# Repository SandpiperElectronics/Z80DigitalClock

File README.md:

# Z80 Digital Clock

## Description:
Built out of a Z80 microcomputer system of my own design, this clock can display Hours, Minutes, and Seconds and does so using an interupt from an Intel 82C53 Counter/Timer chip that is equally as vintage as the Z80.

## To Do: 
- [X] Clock Display
- [X] Clock Display PCB
- [X] Reset Circuit
- [X] Basic Functionality (ROM and CPU)
- [X] 8255 Peripheral Chip
- [X] 8253 Counter/Timer
- [ ] Write Display Sub Routine
- [ ] Clock Sub Routine
- [X] Buttons to Set time
- [ ] Sub routine for button input
- [ ] Z80 Clock PCB

## Images:

### Z80 Clock Schematic (New Version)

### Z80 Clock Schematic (Old Version)

### 7 Segment Peripheral Schematic

### 7 Segment Peripheral Board Design

### 7 Segment PCB and Z80 Clock
.JPG)

### 7 Segments in the Dark
.JPG)

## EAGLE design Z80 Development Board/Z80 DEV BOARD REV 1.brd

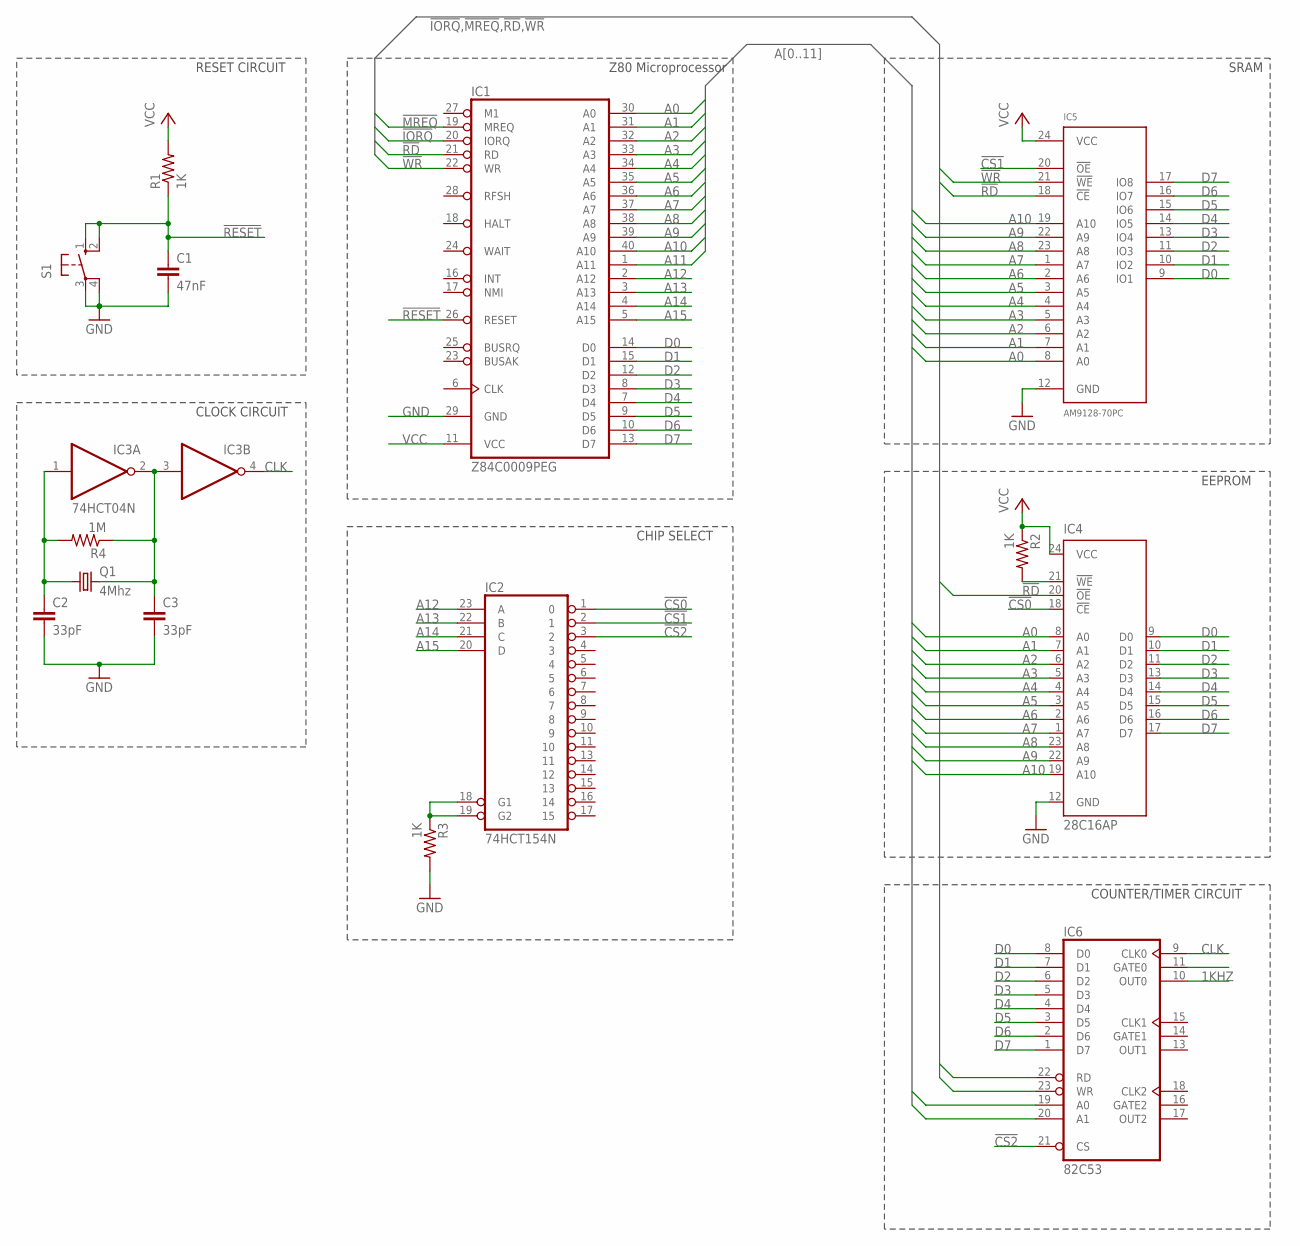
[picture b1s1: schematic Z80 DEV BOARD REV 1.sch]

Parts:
C1: 47nF; C050-035X075
C2, C3: 33pF; C050-035X075
IC1: Z84C0009PEG; DIL40
IC2: 74HCT154N; DIL24-6
IC3: 74HCT04N; DIL14
IC4: 28C16AP; DIL24-6
IC5: AM9128-70PC; DIL24-6
IC6: 82C53; DIL24-6
Q1: 4Mhz; HC49/S
R1, R2, R3: 1K; 0207/7
R4: 1M; 0207/7
S1: 10-XX; B3F-10XX

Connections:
1KHZ: IC6.10 (OUT0)
!CS0: IC2.1 (0), IC4.18 (!CE)
!CS1: IC2.2 (1), IC5.20 (!OE)
!CS2: IC2.3 (2), IC6.21 (CS)
!IORQ: IC1.20 (IORQ)
!MREQ: IC1.19 (MREQ)
!RD: IC1.21 (RD), IC4.20 (!OE), IC5.18 (!CE), IC6.22 (RD)
!RESET: C1.1, IC1.26 (RESET), R1.1, S1.1 (S), S1.2 (S1)
!WR: IC1.22 (WR), IC5.21 (!WE), IC6.23 (WR)
A0: IC1.30 (A0), IC4.8 (A0), IC5.8 (A0), IC6.19 (A0)
A1: IC1.31 (A1), IC4.7 (A1), IC5.7 (A1), IC6.20 (A1)
A2: IC1.32 (A2), IC4.6 (A2), IC5.6 (A2)
A3: IC1.33 (A3), IC4.5 (A3), IC5.5 (A3)
A4: IC1.34 (A4), IC4.4 (A4), IC5.4 (A4)
A5: IC1.35 (A5), IC4.3 (A5), IC5.3 (A5)
A6: IC1.36 (A6), IC4.2 (A6), IC5.2 (A6)
A7: IC1.37 (A7), IC4.1 (A7), IC5.1 (A7)
A8: IC1.38 (A8), IC4.23 (A8), IC5.23 (A8)
A9: IC1.39 (A9), IC4.22 (A9), IC5.22 (A9)
A10: IC1.40 (A10), IC4.19 (A10), IC5.19 (A10)
A11: IC1.1 (A11)
A12: IC1.2 (A12), IC2.23 (A)
A13: IC1.3 (A13), IC2.22 (B)
A14: IC1.4 (A14), IC2.21 (C)
A15: IC1.5 (A15), IC2.20 (D)
CLK: IC3.4 (O), IC6.9 (CLK0)
D0: IC1.14 (D0), IC4.9 (D0), IC5.9 (IO1), IC6.8 (D0)
D1: IC1.15 (D1), IC4.10 (D1), IC5.10 (IO2), IC6.7 (D1)
D2: IC1.12 (D2), IC4.11 (D2), IC5.11 (IO3), IC6.6 (D2)
D3: IC1.8 (D3), IC4.13 (D3), IC5.13 (IO4), IC6.5 (D3)
D4: IC1.7 (D4), IC4.14 (D4), IC5.14 (IO5), IC6.4 (D4)
D5: IC1.9 (D5), IC4.15 (D5), IC5.15 (IO6), IC6.3 (D5)
D6: IC1.10 (D6), IC4.16 (D6), IC5.16 (IO7), IC6.2 (D6)
D7: IC1.13 (D7), IC4.17 (D7), IC5.17 (IO8), IC6.1 (D7)
GND: C1.2, C2.2, C3.2, IC1.29 (GND), IC2.12 (GND), IC3.7 (GND), IC4.12 (GND), IC5.12 (GND), IC6.12 (GND), R3.2, S1.3, S1.4 (P1)
unnamed: C2.1, IC3.1 (I), Q1.1, R4.2
unnamed: IC4.21 (!WE), R2.2
unnamed: C3.1, IC3.2 (O), IC3.3 (I), Q1.2, R4.1
unnamed: IC2.18 (G1), IC2.19 (G2), R3.1
VCC: IC1.11 (VCC), IC2.24 (VCC), IC3.14 (VCC), IC4.24 (VCC), IC5.24 (VCC), IC6.24 (VCC), R1.2, R2.1

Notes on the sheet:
RESET CIRCUIT
Z80 Microprocessor
EEPROM
SRAM
CHIP SELECT
CLOCK CIRCUIT
COUNTER/TIMER CIRCUIT

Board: 2 copper layers, 15 parts (0 on the bottom side), 36 nets, no tracks yet.

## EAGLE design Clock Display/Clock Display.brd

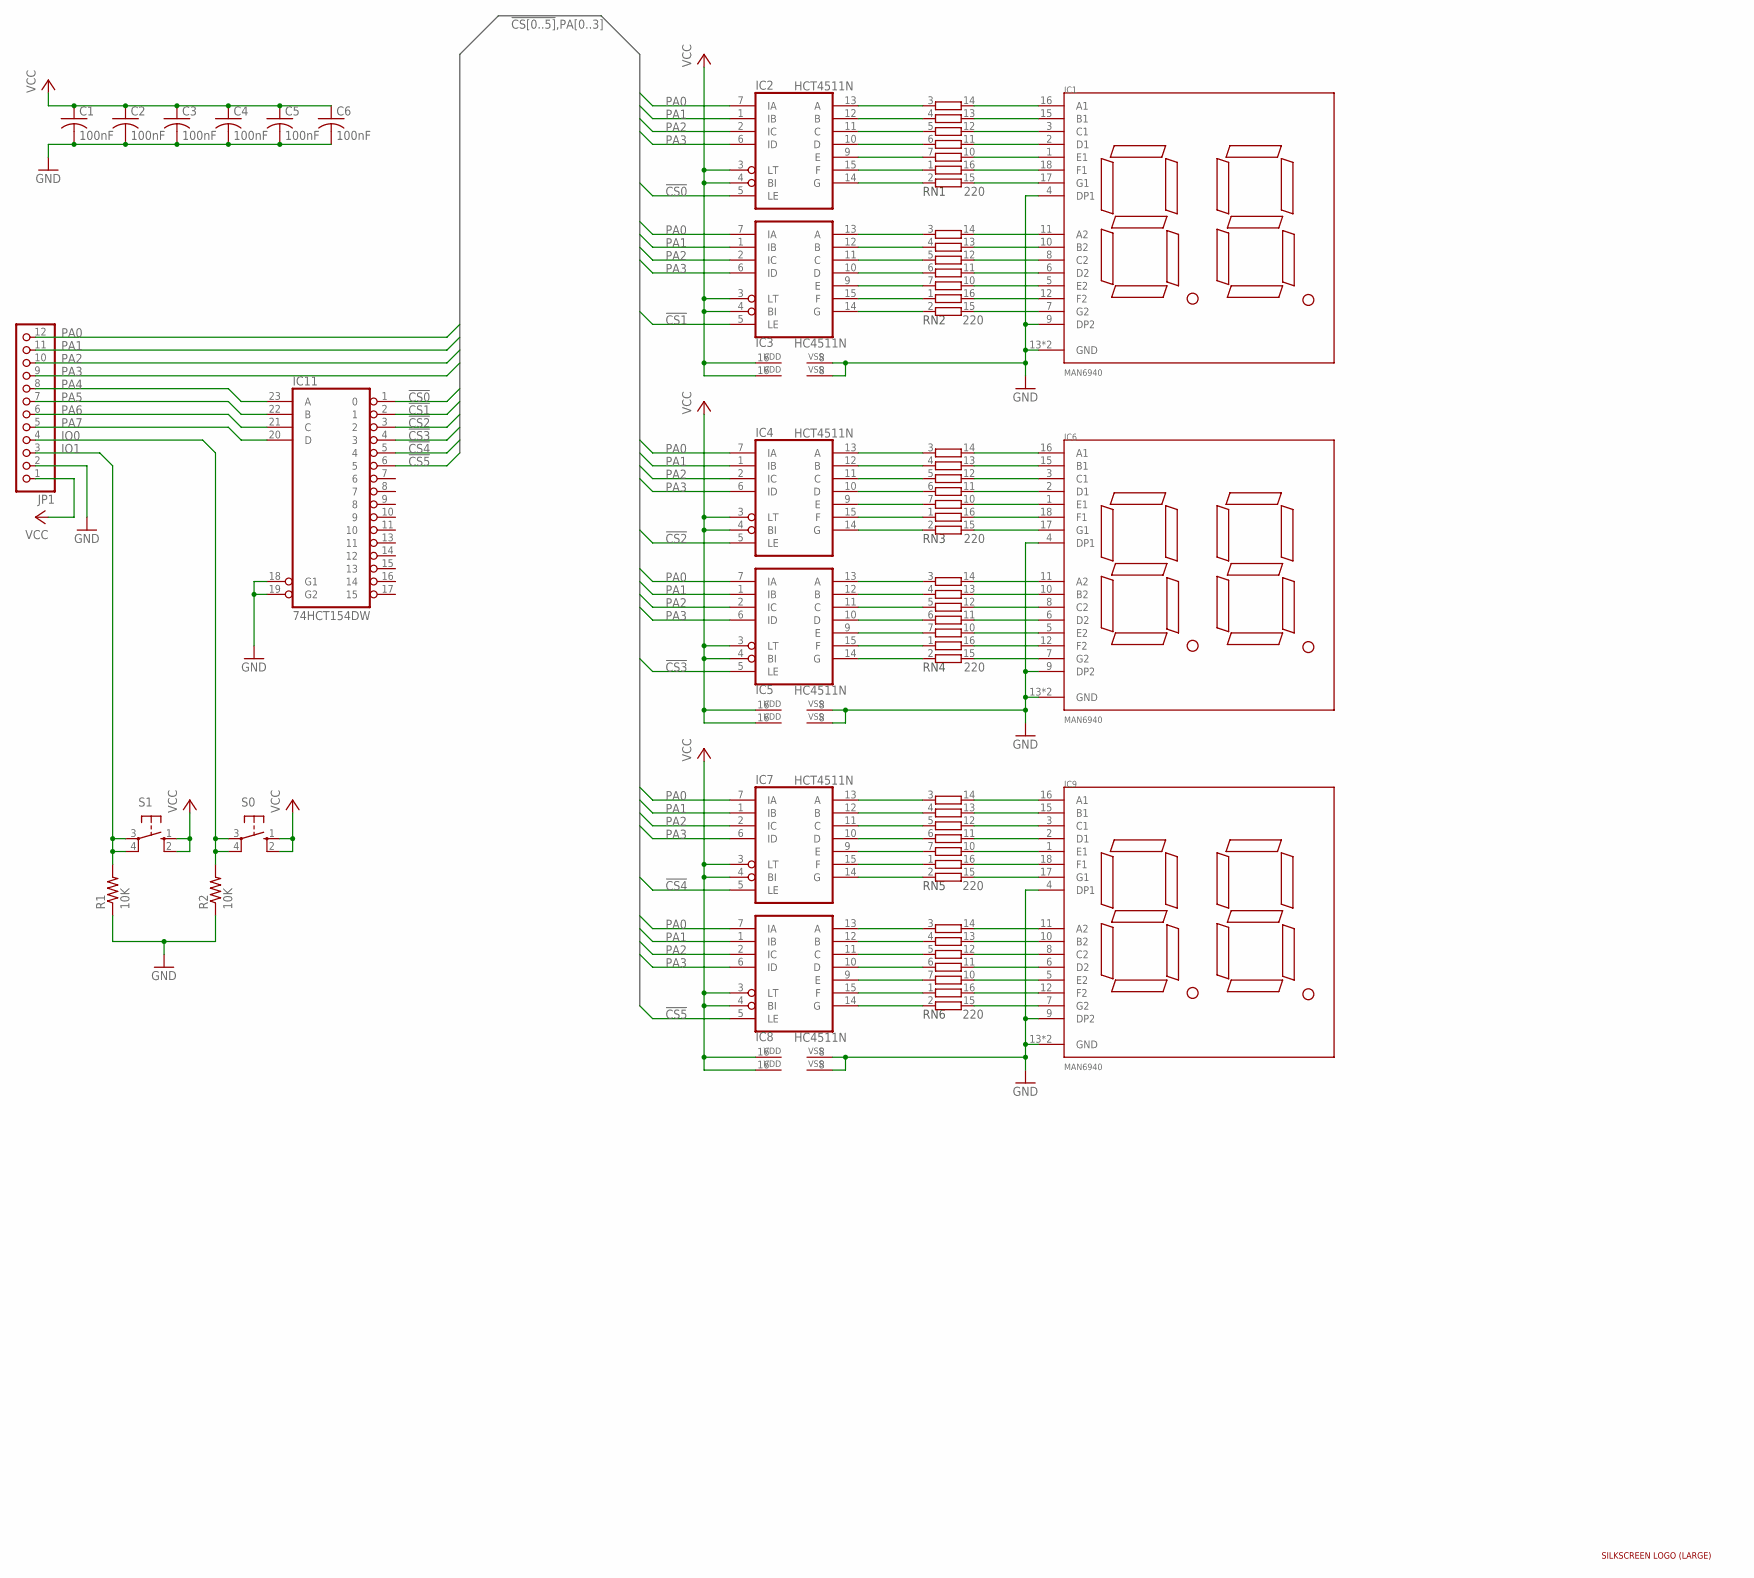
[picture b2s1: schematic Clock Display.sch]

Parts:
C1, C2, C3, C4, C5, C6: 100nF; C0805
IC1, IC6, IC9: MAN6940
IC2, IC4, IC7: HCT4511N; SO16
IC3, IC5, IC8: HC4511N; SO16
IC11: 74HCT154DW; SO24W
JP1: PINHD-1X12-CB; 1X12-CB
R1, R2: 10K; R0805
RN1, RN2, RN3, RN4, RN5, RN6: 220; SOMC16
S0, S1: 10-XX; B3F-10XX
U$1: LOGO_LARGE

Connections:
!CS0: IC2.5 (LE), IC11.1 (0)
!CS1: IC3.5 (LE), IC11.2 (1)
!CS2: IC4.5 (LE), IC11.3 (2)
!CS3: IC5.5 (LE), IC11.4 (3)
!CS4: IC7.5 (LE), IC11.5 (4)
!CS5: IC8.5 (LE), IC11.6 (5)
GND: C1.2, C2.2, C3.2, C4.2, C5.2, C6.2, IC1.4 (DP1), IC1.9 (DP2), IC1.13 (GND), IC1.14 (GND), IC2.8 (VSS), IC3.8 (VSS), IC4.8 (VSS), IC5.8 (VSS), IC6.4 (DP1), IC6.9 (DP2), IC6.13 (GND), IC6.14 (GND), IC7.8 (VSS), IC8.8 (VSS), IC9.4 (DP1), IC9.9 (DP2), IC9.13 (GND), IC9.14 (GND), IC11.12 (GND), IC11.18 (G1), IC11.19 (G2), JP1.2, R1.1, R2.1
IO0: JP1.4, R2.2, S0.3, S0.4 (P1)
IO1: JP1.3, R1.2, S1.3, S1.4 (P1)
unnamed: IC2.13 (A), RN1.3 (1)
unnamed: IC2.12 (B), RN1.4 (1)
unnamed: IC2.11 (C), RN1.5 (1)
unnamed: IC2.10 (D), RN1.6 (1)
unnamed: IC2.9 (E), RN1.7 (1)
unnamed: IC2.15 (F), RN1.1
unnamed: IC2.14 (G), RN1.2 (1)
unnamed: IC3.13 (A), RN2.3 (1)
unnamed: IC3.12 (B), RN2.4 (1)
unnamed: IC3.11 (C), RN2.5 (1)
unnamed: IC3.10 (D), RN2.6 (1)
unnamed: IC3.9 (E), RN2.7 (1)
unnamed: IC3.15 (F), RN2.1
unnamed: IC3.14 (G), RN2.2 (1)
unnamed: IC1.7 (G2), RN2.15 (2)
unnamed: IC1.12 (F2), RN2.16 (2)
unnamed: IC1.5 (E2), RN2.10 (2)
unnamed: IC1.6 (D2), RN2.11 (2)
unnamed: IC1.8 (C2), RN2.12 (2)
unnamed: IC1.10 (B2), RN2.13 (2)
unnamed: IC1.11 (A2), RN2.14 (2)
unnamed: IC1.17 (G1), RN1.15 (2)
unnamed: IC1.18 (F1), RN1.16 (2)
unnamed: IC1.1 (E1), RN1.10 (2)
unnamed: IC1.3 (C1), RN1.12 (2)
unnamed: IC1.2 (D1), RN1.11 (2)
unnamed: IC1.15 (B1), RN1.13 (2)
unnamed: IC1.16 (A1), RN1.14 (2)
unnamed: IC6.16 (A1), RN3.14 (2)
unnamed: IC6.15 (B1), RN3.13 (2)
unnamed: IC6.3 (C1), RN3.12 (2)
unnamed: IC6.2 (D1), RN3.11 (2)
unnamed: IC6.1 (E1), RN3.10 (2)
unnamed: IC6.18 (F1), RN3.16 (2)
unnamed: IC6.17 (G1), RN3.15 (2)
unnamed: IC6.11 (A2), RN4.14 (2)
unnamed: IC6.10 (B2), RN4.13 (2)
unnamed: IC6.8 (C2), RN4.12 (2)
unnamed: IC6.6 (D2), RN4.11 (2)
unnamed: IC6.5 (E2), RN4.10 (2)
unnamed: IC6.12 (F2), RN4.16 (2)
unnamed: IC6.7 (G2), RN4.15 (2)
unnamed: IC4.13 (A), RN3.3 (1)
unnamed: IC4.12 (B), RN3.4 (1)
unnamed: IC4.11 (C), RN3.5 (1)
unnamed: IC4.10 (D), RN3.6 (1)
unnamed: IC4.9 (E), RN3.7 (1)
unnamed: IC4.15 (F), RN3.1
unnamed: IC4.14 (G), RN3.2 (1)
unnamed: IC5.13 (A), RN4.3 (1)
unnamed: IC5.12 (B), RN4.4 (1)
unnamed: IC5.11 (C), RN4.5 (1)
unnamed: IC5.10 (D), RN4.6 (1)
unnamed: IC5.9 (E), RN4.7 (1)
unnamed: IC5.15 (F), RN4.1
unnamed: IC5.14 (G), RN4.2 (1)
unnamed: IC9.16 (A1), RN5.14 (2)
unnamed: IC9.15 (B1), RN5.13 (2)
unnamed: IC9.3 (C1), RN5.12 (2)
unnamed: IC9.2 (D1), RN5.11 (2)
unnamed: IC9.1 (E1), RN5.10 (2)
unnamed: IC9.18 (F1), RN5.16 (2)
unnamed: IC9.17 (G1), RN5.15 (2)
unnamed: IC9.11 (A2), RN6.14 (2)
unnamed: IC9.10 (B2), RN6.13 (2)
unnamed: IC9.8 (C2), RN6.12 (2)
unnamed: IC9.6 (D2), RN6.11 (2)
unnamed: IC9.5 (E2), RN6.10 (2)
unnamed: IC9.12 (F2), RN6.16 (2)
unnamed: IC9.7 (G2), RN6.15 (2)
unnamed: IC7.13 (A), RN5.3 (1)
unnamed: IC7.12 (B), RN5.4 (1)
unnamed: IC7.11 (C), RN5.5 (1)
unnamed: IC7.10 (D), RN5.6 (1)
unnamed: IC7.9 (E), RN5.7 (1)
unnamed: IC7.15 (F), RN5.1
unnamed: IC7.14 (G), RN5.2 (1)
unnamed: IC8.13 (A), RN6.3 (1)
unnamed: IC8.12 (B), RN6.4 (1)
unnamed: IC8.11 (C), RN6.5 (1)
unnamed: IC8.10 (D), RN6.6 (1)
unnamed: IC8.9 (E), RN6.7 (1)
unnamed: IC8.15 (F), RN6.1
unnamed: IC8.14 (G), RN6.2 (1)
PA0: IC2.7 (IA), IC3.7 (IA), IC4.7 (IA), IC5.7 (IA), IC7.7 (IA), IC8.7 (IA), JP1.12
PA1: IC2.1 (IB), IC3.1 (IB), IC4.1 (IB), IC5.1 (IB), IC7.1 (IB), IC8.1 (IB), JP1.11
PA2: IC2.2 (IC), IC3.2 (IC), IC4.2 (IC), IC5.2 (IC), IC7.2 (IC), IC8.2 (IC), JP1.10
PA3: IC2.6 (ID), IC3.6 (ID), IC4.6 (ID), IC5.6 (ID), IC7.6 (ID), IC8.6 (ID), JP1.9
PA4: IC11.23 (A), JP1.8
PA5: IC11.22 (B), JP1.7
PA6: IC11.21 (C), JP1.6
PA7: IC11.20 (D), JP1.5
VCC: C1.1, C2.1, C3.1, C4.1, C5.1, C6.1, IC2.3 (LT), IC2.4 (BI), IC2.16 (VDD), IC3.3 (LT), IC3.4 (BI), IC3.16 (VDD), IC4.3 (LT), IC4.4 (BI), IC4.16 (VDD), IC5.3 (LT), IC5.4 (BI), IC5.16 (VDD), IC7.3 (LT), IC7.4 (BI), IC7.16 (VDD), IC8.3 (LT), IC8.4 (BI), IC8.16 (VDD), IC11.24 (VCC), JP1.1, S0.1 (S), S0.2 (S1), S1.1 (S), S1.2 (S1)

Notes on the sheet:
RN1
RN2
RN3
RN4
RN5
RN6

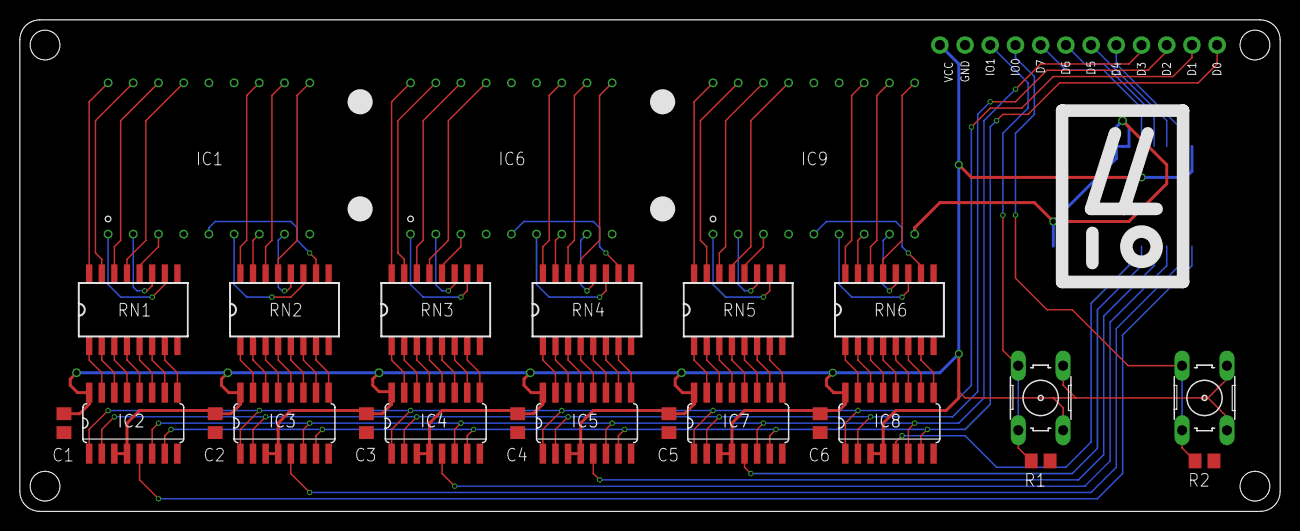
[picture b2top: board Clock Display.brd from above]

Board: 2 copper layers, 127.0 x 49.5 mm, 28 parts (1 on the bottom side), 102 nets.

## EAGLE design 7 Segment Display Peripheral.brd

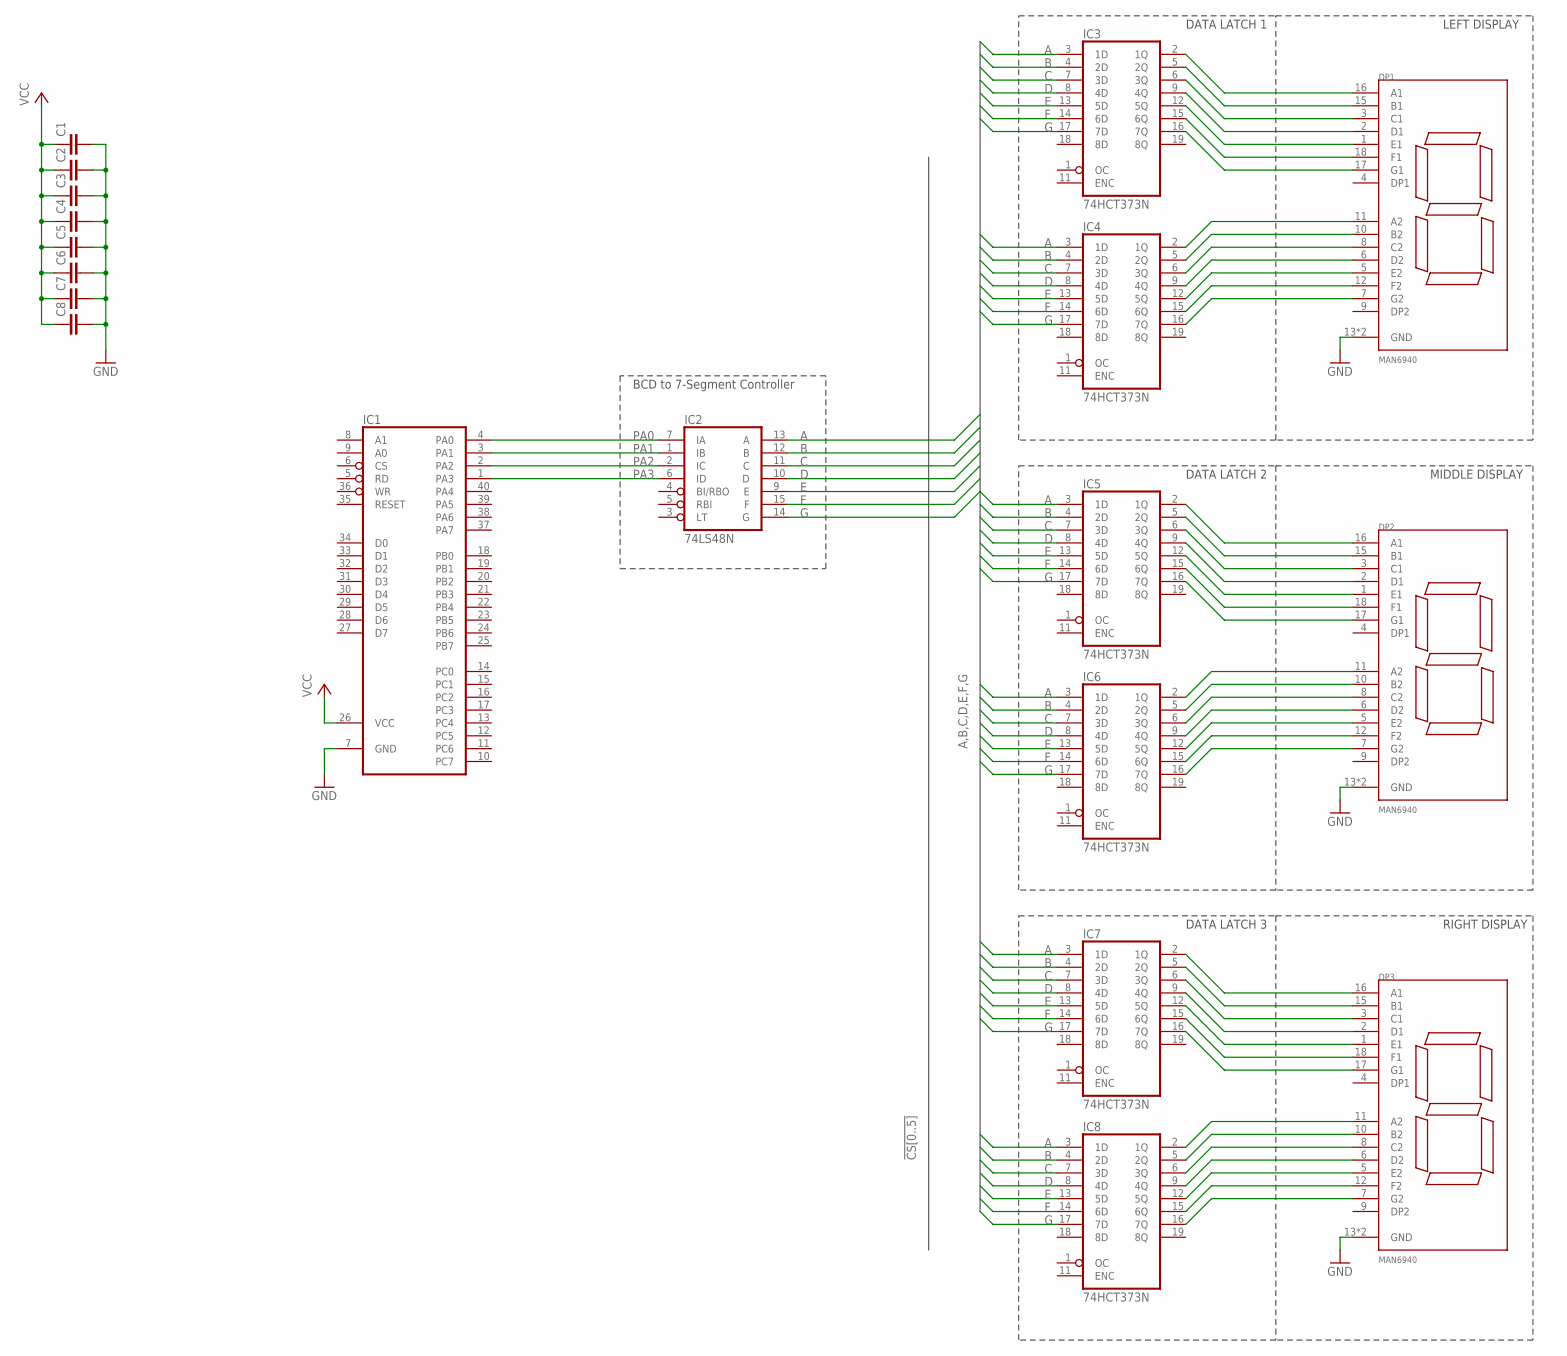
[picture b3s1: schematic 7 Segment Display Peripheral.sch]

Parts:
C1, C2, C3, C4, C5, C6, C7, C8: C-EU050-024X044; C050-024X044
DP1, DP2, DP3: MAN6940
IC1: 82C55A; DIL40
IC2: 74LS48N; DIL16
IC3, IC4, IC5, IC6, IC7, IC8: 74HCT373N; DIL20

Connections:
A: IC2.13 (A), IC3.3 (1D), IC4.3 (1D), IC5.3 (1D), IC6.3 (1D), IC7.3 (1D), IC8.3 (1D)
B: IC2.12 (B), IC3.4 (2D), IC4.4 (2D), IC5.4 (2D), IC6.4 (2D), IC7.4 (2D), IC8.4 (2D)
C: IC2.11 (C), IC3.7 (3D), IC4.7 (3D), IC5.7 (3D), IC6.7 (3D), IC7.7 (3D), IC8.7 (3D)
D: IC2.10 (D), IC3.8 (4D), IC4.8 (4D), IC5.8 (4D), IC6.8 (4D), IC7.8 (4D), IC8.8 (4D)
E: IC2.9 (E), IC3.13 (5D), IC4.13 (5D), IC5.13 (5D), IC6.13 (5D), IC7.13 (5D), IC8.13 (5D)
F: IC2.15 (F), IC3.14 (6D), IC4.14 (6D), IC5.14 (6D), IC6.14 (6D), IC7.14 (6D), IC8.14 (6D)
G: IC2.14 (G), IC3.17 (7D), IC4.17 (7D), IC5.17 (7D), IC6.17 (7D), IC7.17 (7D), IC8.17 (7D)
GND: C1.2, C2.2, C3.2, C4.2, C5.2, C6.2, C7.2, C8.2, DP1.13 (GND), DP1.14 (GND), DP2.13 (GND), DP2.14 (GND), DP3.13 (GND), DP3.14 (GND), IC1.7 (GND), IC2.8 (GND), IC3.10 (GND), IC4.10 (GND), IC5.10 (GND), IC6.10 (GND), IC7.10 (GND), IC8.10 (GND)
unnamed: DP1.17 (G1), IC3.16 (7Q)
unnamed: DP1.18 (F1), IC3.15 (6Q)
unnamed: DP1.1 (E1), IC3.12 (5Q)
unnamed: DP1.2 (D1), IC3.9 (4Q)
unnamed: DP1.3 (C1), IC3.6 (3Q)
unnamed: DP1.15 (B1), IC3.5 (2Q)
unnamed: DP1.16 (A1), IC3.2 (1Q)
unnamed: DP1.11 (A2), IC4.2 (1Q)
unnamed: DP1.10 (B2), IC4.5 (2Q)
unnamed: DP1.8 (C2), IC4.6 (3Q)
unnamed: DP1.6 (D2), IC4.9 (4Q)
unnamed: DP1.5 (E2), IC4.12 (5Q)
unnamed: DP1.12 (F2), IC4.15 (6Q)
unnamed: DP1.7 (G2), IC4.16 (7Q)
unnamed: DP2.17 (G1), IC5.16 (7Q)
unnamed: DP2.18 (F1), IC5.15 (6Q)
unnamed: DP2.1 (E1), IC5.12 (5Q)
unnamed: DP2.2 (D1), IC5.9 (4Q)
unnamed: DP2.3 (C1), IC5.6 (3Q)
unnamed: DP2.15 (B1), IC5.5 (2Q)
unnamed: DP2.16 (A1), IC5.2 (1Q)
unnamed: DP2.11 (A2), IC6.2 (1Q)
unnamed: DP2.10 (B2), IC6.5 (2Q)
unnamed: DP2.8 (C2), IC6.6 (3Q)
unnamed: DP2.6 (D2), IC6.9 (4Q)
unnamed: DP2.5 (E2), IC6.12 (5Q)
unnamed: DP2.12 (F2), IC6.15 (6Q)
unnamed: DP2.7 (G2), IC6.16 (7Q)
unnamed: DP3.17 (G1), IC7.16 (7Q)
unnamed: DP3.18 (F1), IC7.15 (6Q)
unnamed: DP3.1 (E1), IC7.12 (5Q)
unnamed: DP3.2 (D1), IC7.9 (4Q)
unnamed: DP3.3 (C1), IC7.6 (3Q)
unnamed: DP3.15 (B1), IC7.5 (2Q)
unnamed: DP3.16 (A1), IC7.2 (1Q)
unnamed: DP3.11 (A2), IC8.2 (1Q)
unnamed: DP3.10 (B2), IC8.5 (2Q)
unnamed: DP3.8 (C2), IC8.6 (3Q)
unnamed: DP3.6 (D2), IC8.9 (4Q)
unnamed: DP3.5 (E2), IC8.12 (5Q)
unnamed: DP3.12 (F2), IC8.15 (6Q)
unnamed: DP3.7 (G2), IC8.16 (7Q)
PA0: IC1.4 (PA0), IC2.7 (IA)
PA1: IC1.3 (PA1), IC2.1 (IB)
PA2: IC1.2 (PA2), IC2.2 (IC)
PA3: IC1.1 (PA3), IC2.6 (ID)
VCC: C1.1, C2.1, C3.1, C4.1, C5.1, C6.1, C7.1, C8.1, IC1.26 (VCC), IC2.16 (VCC), IC3.20 (VCC), IC4.20 (VCC), IC5.20 (VCC), IC6.20 (VCC), IC7.20 (VCC), IC8.20 (VCC)

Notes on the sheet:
LEFT DISPLAY
MIDDLE DISPLAY
RIGHT DISPLAY
BCD to 7-Segment Controller
DATA LATCH 1
DATA LATCH 2
DATA LATCH 3

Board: 2 copper layers, 19 parts (0 on the bottom side), 55 nets, no tracks yet.

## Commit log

2020-08-16 Early Version of the 7-Segment Display Peripheral
    This was an early prototype of the 7-Segment Display Peripheral used to construct the breadboard version of the circuit. I switched to surface mount components for the final version of this periphera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
2020-08-16 Rename 7 Segment Display Peripheral.brd to Clock Display/7 Segment Display Peripheral.brd
2020-08-16 Rename 7 Segment Display Peripheral.sch to Clock Display/7 Segment Display Peripheral.sch
2020-08-16 Images of z80 Clock
2020-08-16 Z80 Clock Images Documenting Progress
2020-08-16 added images
2022-02-27 Uploaded Z80 Clock Code V2
    Improvements on readability.
    Implement a count by millisecond instead of seconds for increased accuracy in addition to only using a single counter output.
2022-02-27 Delete Z80 Clock Rev 1.bin
    old code
